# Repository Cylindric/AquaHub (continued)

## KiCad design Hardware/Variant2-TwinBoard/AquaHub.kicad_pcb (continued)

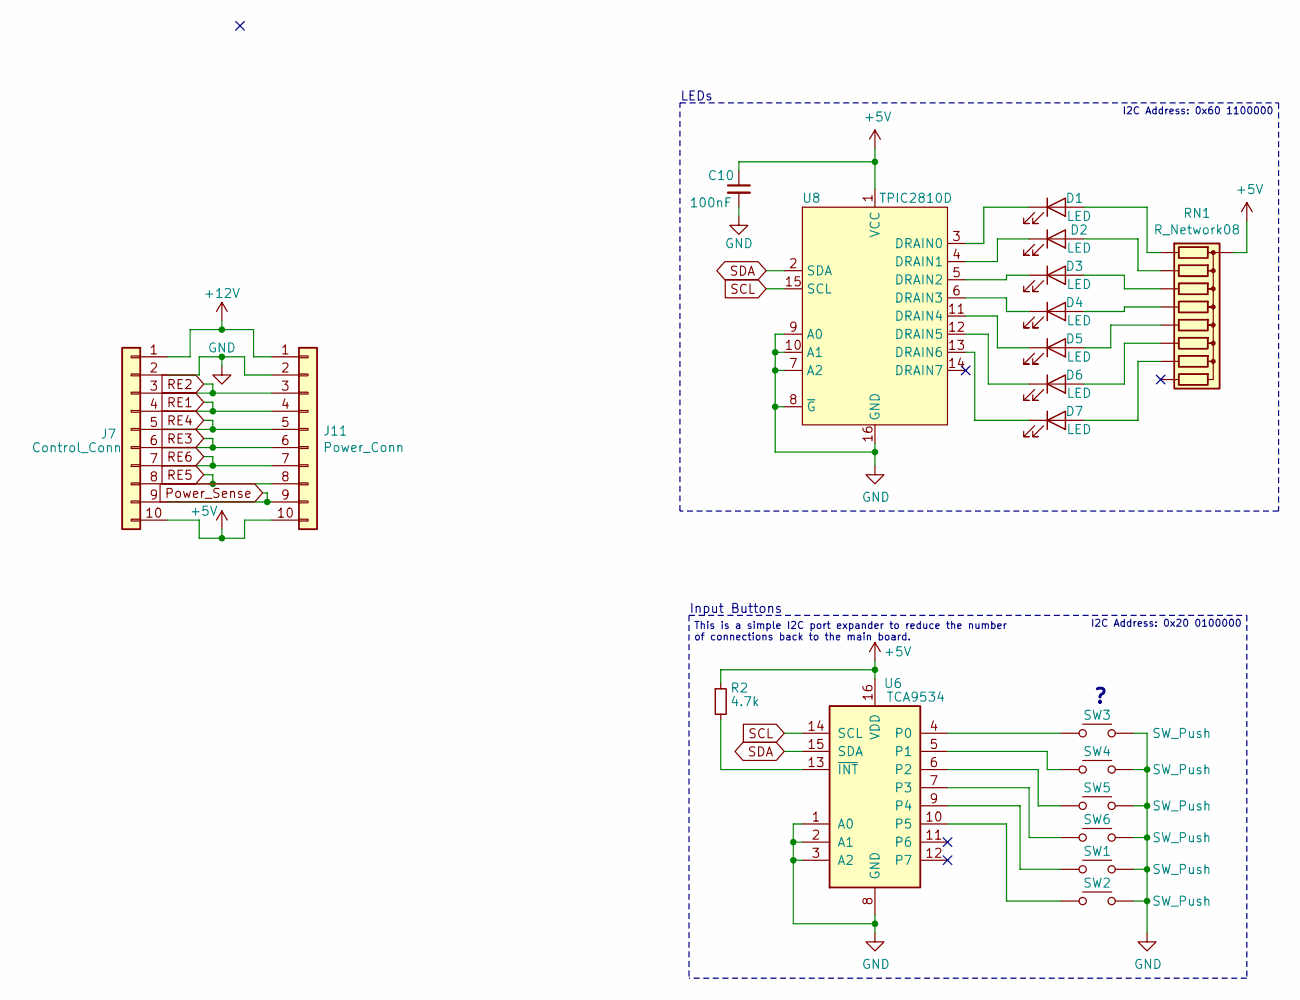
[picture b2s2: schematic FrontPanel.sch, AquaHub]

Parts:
C10: 100nF; C_0603_1608Metric_Pad1.05x0.95mm_HandSolder
D1, D2, D3, D4, D5, D6, D7: LED; LED_D5.0mm
J7: Control_Conn; IDC-Header_2x05_P2.54mm_Vertical
J11: Power_Conn; IDC-Header_2x05_P2.54mm_Vertical
R2: 4.7k; R_0603_1608Metric_Pad1.05x0.95mm_HandSolder
RN1: R_Network08; CAT25
SW1, SW2, SW3, SW4, SW5, SW6: SW_Push; SW_CK_D6R_SPST_12mm_H14.3mm
U6: TCA9534; SOIC-16W_7.5x10.3mm_P1.27mm
U8: TPIC2810D; SOIC-16_3.9x9.9mm_P1.27mm

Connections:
+5V: C10.1, J7.10, J11.10, R2.1, RN1.1 (common), U6.16 (VDD), U8.1 (VCC); also elsewhere on the board
+12V: J7.1, J11.1; also elsewhere on the board
GND: C10.2, J7.2, J11.2, SW1.2 (B), SW1.4 (B), SW2.2 (B), SW2.4 (B), SW3.2 (B), SW3.4 (B), SW4.2 (B), SW4.4 (B), SW5.2 (B), SW5.4 (B), SW6.2 (B), SW6.4 (B), U6.1 (A0), U6.2 (A1), U6.3 (A2), U6.8 (GND), U8.7 (A2), U8.8 (~G), U8.9 (A0), U8.10 (A1), U8.16 (GND); also elsewhere on the board
unnamed: D1.1 (K), U8.3 (DRAIN0)
unnamed: D1.2 (A), RN1.2 (R1)
unnamed: D2.1 (K), U8.4 (DRAIN1)
unnamed: D2.2 (A), RN1.3 (R2)
unnamed: D3.1 (K), U8.5 (DRAIN2)
unnamed: D3.2 (A), RN1.4 (R3)
unnamed: D4.1 (K), U8.6 (DRAIN3)
unnamed: D4.2 (A), RN1.5 (R4)
unnamed: D5.1 (K), U8.11 (DRAIN4)
unnamed: D5.2 (A), RN1.6 (R5)
unnamed: D6.1 (K), U8.12 (DRAIN5)
unnamed: D6.2 (A), RN1.7 (R6)
unnamed: D7.1 (K), U8.13 (DRAIN6)
unnamed: D7.2 (A), RN1.8 (R7)
unnamed: R2.2, U6.13 (~INT~)
unnamed: SW1.1 (A), SW1.3 (A), U6.9 (P4)
unnamed: SW2.1 (A), SW2.3 (A), U6.10 (P5)
unnamed: SW3.1 (A), SW3.3 (A), U6.4 (P0)
unnamed: SW4.1 (A), SW4.3 (A), U6.5 (P1)
unnamed: SW5.1 (A), SW5.3 (A), U6.6 (P2)
unnamed: SW6.1 (A), SW6.3 (A), U6.7 (P3)
Power_Sense: J7.9, J11.9; also elsewhere on the board
RE1: J7.4, J11.4; also elsewhere on the board
RE2: J7.3, J11.3; also elsewhere on the board
RE3: J7.6, J11.6; also elsewhere on the board
RE4: J7.5, J11.5; also elsewhere on the board
RE5: J7.8, J11.8; also elsewhere on the board
RE6: J7.7, J11.7; also elsewhere on the board
SCL: U6.14 (SCL), U8.15 (SCL); also elsewhere on the board
SDA: U6.15 (SDA), U8.2 (SDA); also elsewhere on the board

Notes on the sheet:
Input Buttons
This is a simple I2C port expander to reduce the number of connections back to the main board.
LEDs
I2C Address: 0x60 1100000
I2C Address: 0x20 0100000

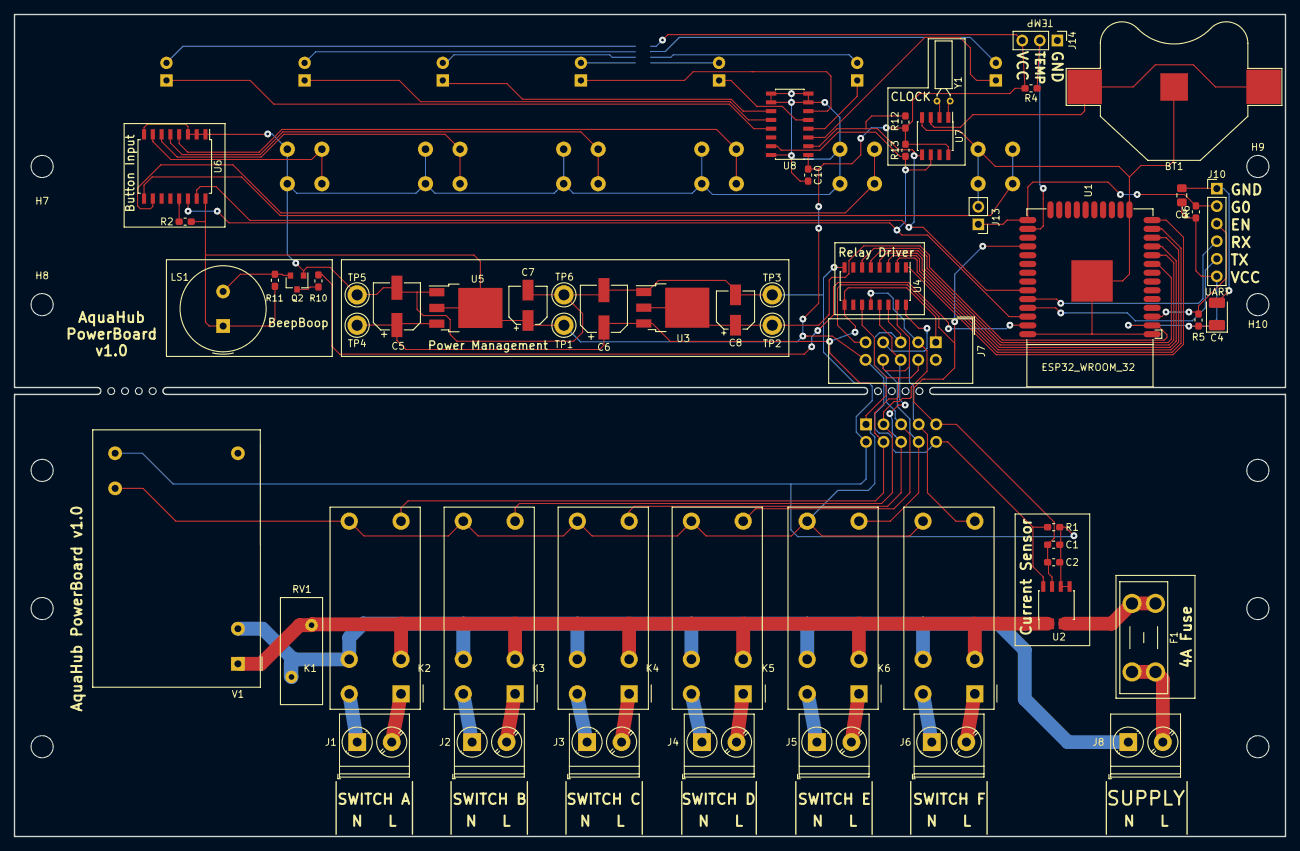
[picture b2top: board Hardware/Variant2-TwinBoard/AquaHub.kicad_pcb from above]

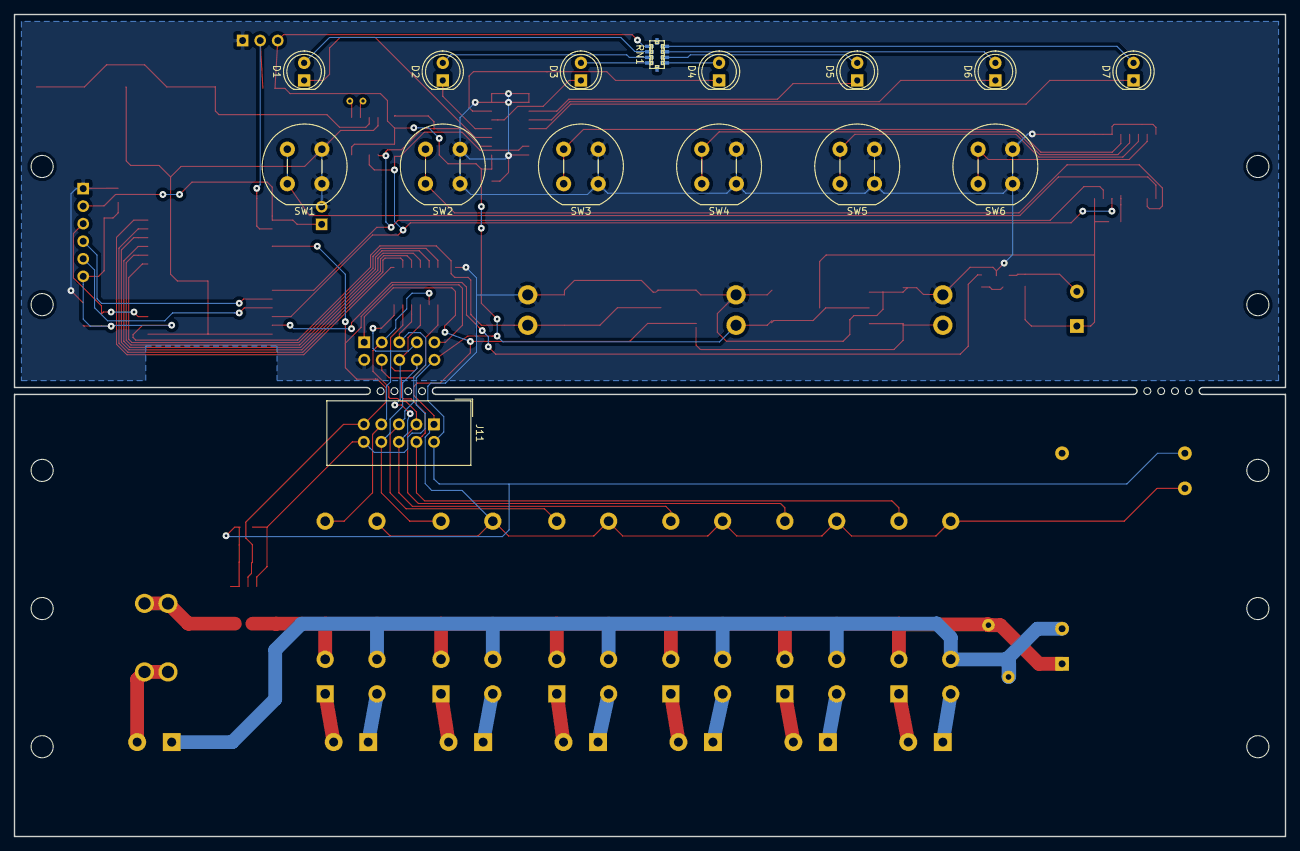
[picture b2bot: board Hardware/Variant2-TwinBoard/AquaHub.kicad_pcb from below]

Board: 2 copper layers, 184.0 x 119.0 mm, 89 parts (15 on the bottom side), 67 nets.

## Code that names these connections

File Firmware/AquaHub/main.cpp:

#include "Arduino.h"
// #include <ArduinoOTA.h>
// #include <WiFi.h>
// #include <WiFiMulti.h>
// #include <WiFiUdp.h>

int RTC_I2C_ADDR = 0x68; // 1101000
int LED_I2C_ADDR = 0x60; // 1100000
int BTN_I2C_ADDR = 0x20; // 0100000

// Pins
int I2C_SCL   = 36; // IO22, pin 36
int I2C_SDA   = 33; // IO21, pin 33
int PWR_SENSE = 28; // IO17, pin 28
int TMP_SENSE = 26; // IO4,  pin 26
int SOUND_PIN = 37; // IO23, pin 37

int POW1 =  9; // IO33, pin 9
int POW2 = 10; // IO25, pin 10
int POW3 = 11; // IO26, pin 11
int POW4 = 12; // IO27, pin 12
int POW5 = 13; // IO14, pin 13
int POW6 = 14; // IO12, pin 14

// #if CONFIG_AUTOSTART_ARDUINO

// #if CONFIG_FREERTOS_UNICORE
// #define ARDUINO_RUNNING_CORE 0
// #else
// #define ARDUINO_RUNNING_CORE 1
// #endif

// void loopTask(void *pvParameters)
// {
//     setup();
//     for(;;) {
//         micros(); //update overflow
//         loop();
//     }
// }

// void app_main()
// {
//     initArduino();
//     xTaskCreatePinnedToCore(loopTask, "loopTask", 8192, NULL, 1, NULL, ARDUINO_RUNNING_CORE);
// }

// #endif


void setup() {
  // put your setup code here, to run once:
  Serial.begin(115200);
}

void loop() {
  // put your main code here, to run repeatedly:
  Serial.println("loop");
  delay(1000);
}

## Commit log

2018-09-09 Lots of new stuff
2018-09-10 Added OHL. Removed old board Step. Removed old outputs
2018-09-10 Added latest output
2018-09-12 Auto-generated Outputs
2018-09-12 Update README.md
    Add link to vendor project.
2018-09-16 Many refinements
2018-09-17 Various changes
2018-09-23 Removed a bunch of old datasheets
2018-09-30 Various updates and tweaks
2018-10-02 Updated for parts now in stdlib
2018-10-04 Before trying a single-board
2018-10-14 Split different layout schemes
2018-10-15 New TwinBoard layout
2018-10-15 Removed old variants
2018-10-15 Removed old files
2018-10-19 Prep for first manufacturing run
2018-10-23 Removing datasheets from the repo.
2018-10-23 Updated readme.
2018-10-23 Firmware structure
2018-10-25 Add license scan report and status
2018-10-25 Switch the software license to Apache 2
2018-10-25 Update license to apache 2
2018-10-25 Trying out Travis
2018-10-25 Fixed Travis name
2018-10-25 Trying newer arduino
2018-10-25 Fixing build
2018-10-25 Adding ESP32
2018-10-25 Switch to IDF compile
2018-10-25 Enable C++ exceptions
2018-10-26 Switching to docker
2018-10-26 Adding components
2018-10-26 Missing env?
2018-10-26 Trying things out.
2018-10-26 Checking docker
2018-10-26 Trying to fix docker...
2018-10-26 Not running is a bit odd
2018-10-26 You got this.
2018-10-26 You don't got this.
2018-10-27 Commit latest hardware updates and initial firmware
2018-10-27 Remove ESP-IDF files from the non-IDF branch
2018-10-27 RelayControl framework
2018-10-27 Removed old BOM
2018-10-28 Moved vscode directory
2018-10-28 Initial LED control
2018-10-28 Some more framework
2018-10-29 Updated travis file
2018-10-30 Missed sdkconfig
2018-10-30 Added some forward decs
2018-10-30 Added some more framework
2018-10-31 Switched to IDF branch
2018-10-31 Basic web server framework
2018-11-01 Added some webserver stuff
2018-11-02 Trying out the Vue framework
2018-11-04 Lots of firmware updates
2018-11-04 Big PCB switch to a single board. Again.
2018-11-17 Finalising the Rev2 hardware.
2018-11-17 A bit of firmware
